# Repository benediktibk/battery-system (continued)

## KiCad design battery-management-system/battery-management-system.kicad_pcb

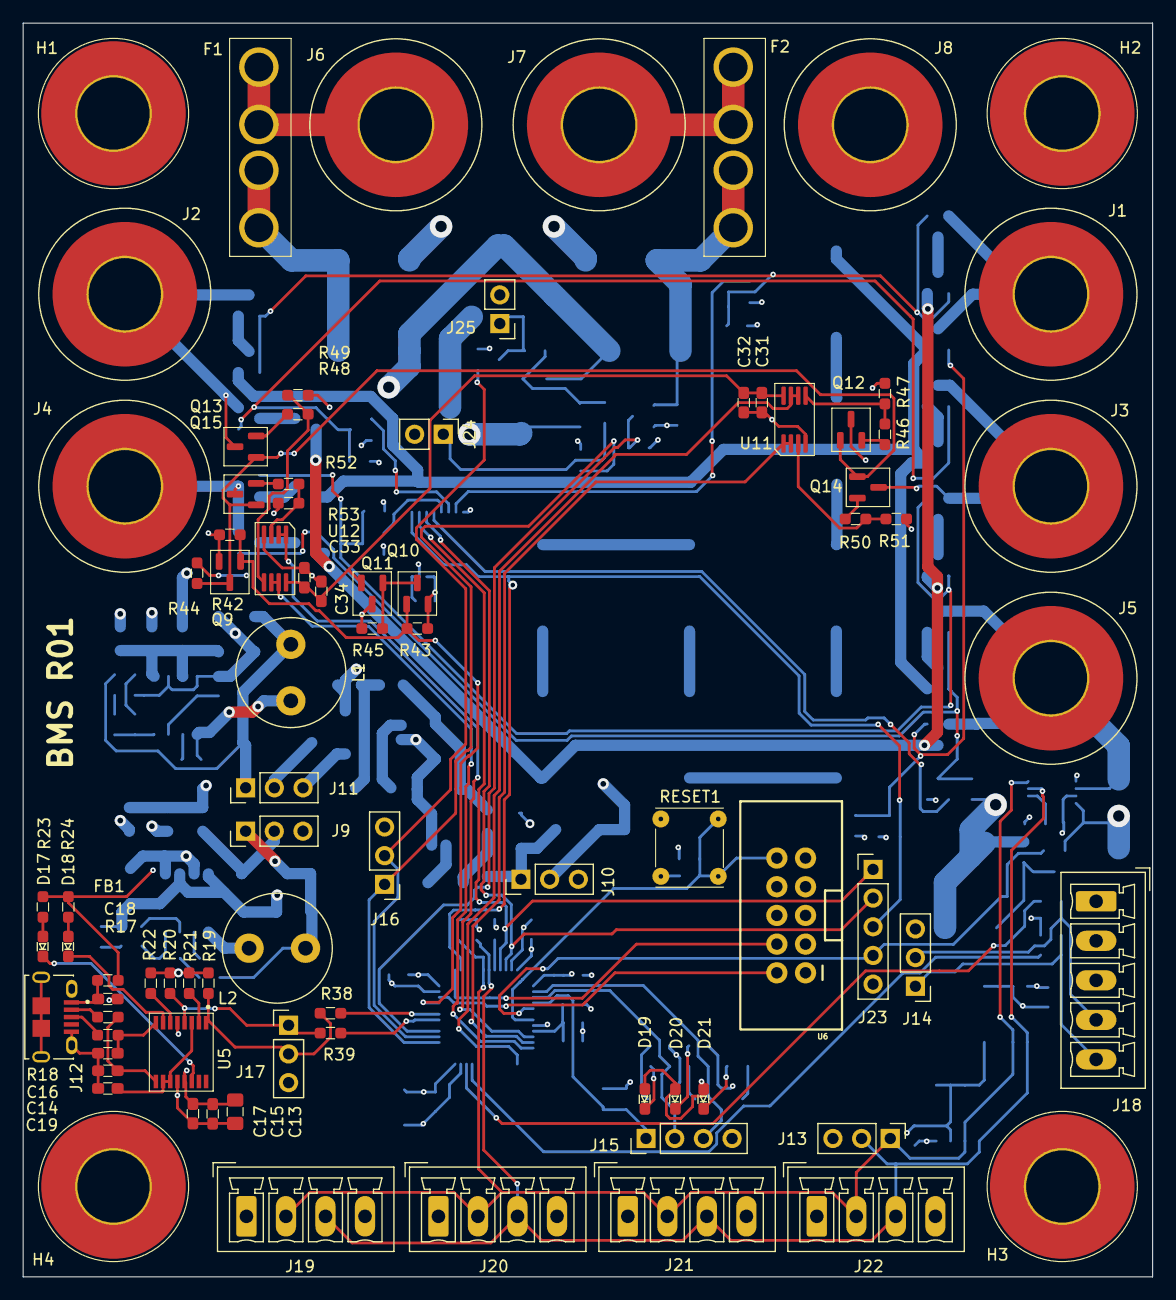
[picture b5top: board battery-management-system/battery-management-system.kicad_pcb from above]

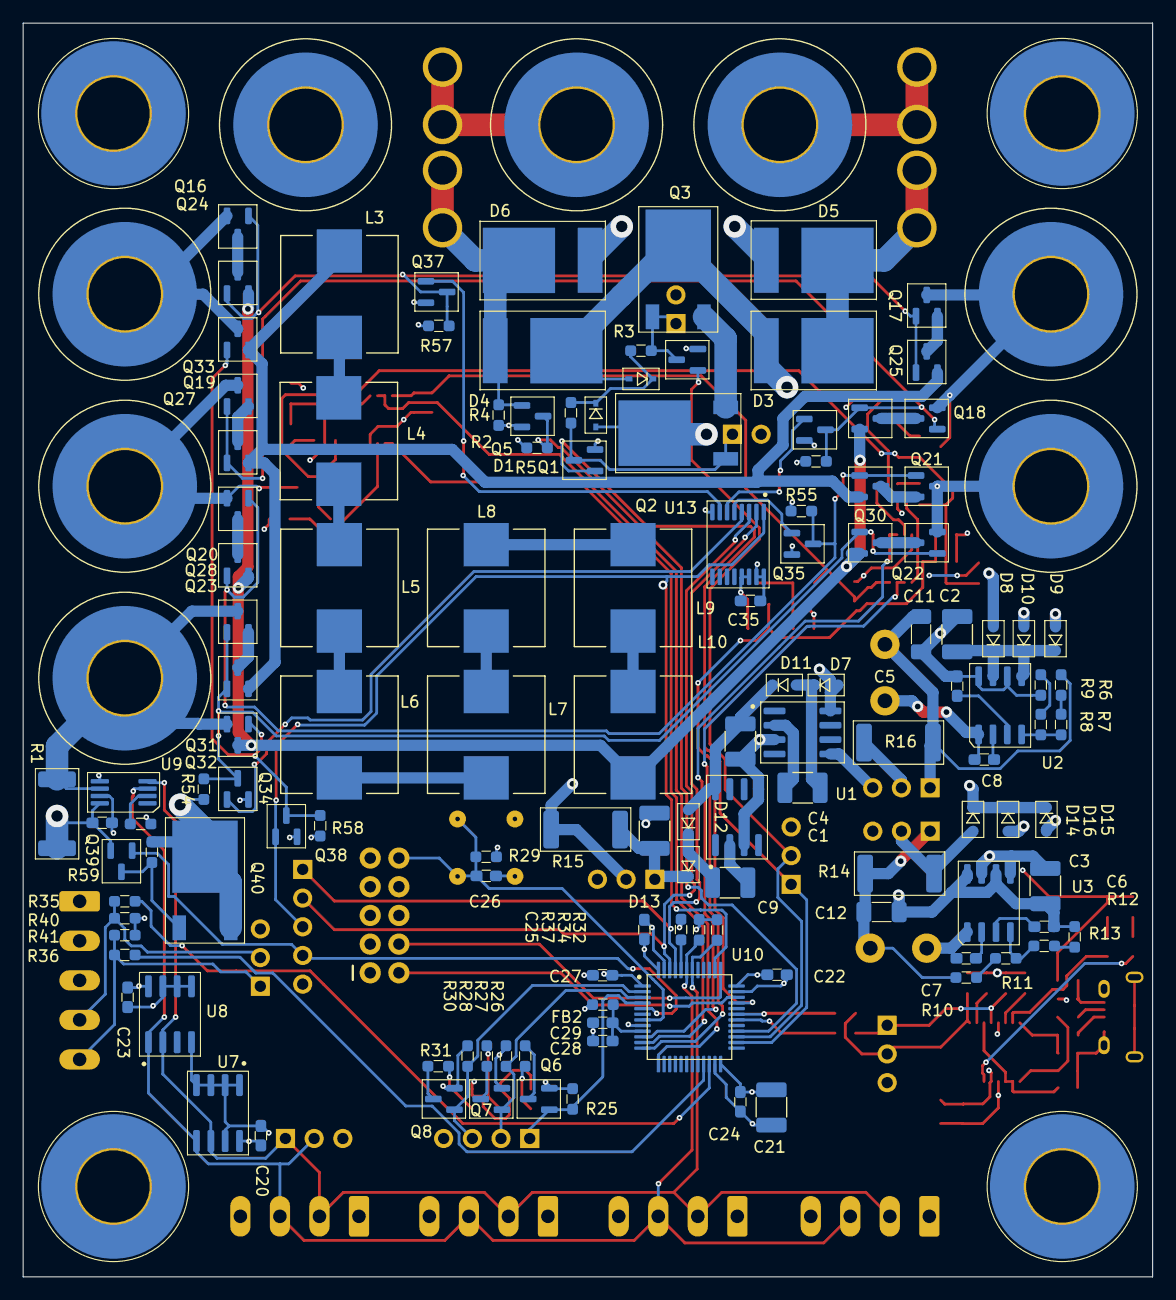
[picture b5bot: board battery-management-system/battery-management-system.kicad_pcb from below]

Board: 4 copper layers, 100.0 x 111.0 mm, 212 parts (128 on the bottom side), 129 nets.

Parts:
C1, C2, C3, C4, C9, C10, C21: 10uF; C_1210_3225Metric_Pad1.33x2.70mm_HandSolder
C5, C6, C29, C30, C32, C34: 1uF; C_0603_1608Metric_Pad1.08x0.95mm_HandSolder
C7, C8, C15, C17, C19, C20, C22, C23, C24, C25, C26, C27, C28, C31, C33, C35: 100nF; C_0603_1608Metric_Pad1.08x0.95mm_HandSolder
C11, C12: 47uF; C_1206_3216Metric_Pad1.33x1.80mm_HandSolder
C13: 4.7uF; C_0805_2012Metric_Pad1.18x1.45mm_HandSolder
C14, C16: 47pF; C_0603_1608Metric_Pad1.08x0.95mm_HandSolder
C18: 10nF; C_0603_1608Metric_Pad1.08x0.95mm_HandSolder
D1, D2, D7, D8, D9, D10, D11, D12, D13, D14, D15, D16: BAT54WS; D_SOD-323
D3, D4, D5, D6: SBR2065D1
D17: UART_TX; D_0603_1608Metric_Pad1.05x0.95mm_HandSolder
D18: UART_RX; D_0603_1608Metric_Pad1.05x0.95mm_HandSolder
D19: green; D_0603_1608Metric_Pad1.05x0.95mm_HandSolder
D20: red; D_0603_1608Metric_Pad1.05x0.95mm_HandSolder
D21: yellow; D_0603_1608Metric_Pad1.05x0.95mm_HandSolder
F1, F2: 20A; KEYSTONE_blade_fus_holder
FB1, FB2: BLM18P; R_0603_1608Metric_Pad0.98x0.95mm_HandSolder
H1, H2, H3, H4: MountingHole_Pad; MountingHole_6.4mm_M6_Pad_TopBottom
J1: CELL4_PLUS; Connector_M6
J2: CELL4_MINUS; Connector_M6
J3: CELL3_MINUS; Connector_M6
J4: CELL2_MINUS; Connector_M6
J5: CELL1_MINUS; Connector_M6
J6: VBAT+; Connector_M6
J7: VBAT+_CHARGE; Connector_M6
J8: VBAT-; Connector_M6
J9: 5V; PinHeader_1x03_P2.54mm_Vertical
J10: 18V; PinHeader_1x03_P2.54mm_Vertical
J11: 3V3; PinHeader_1x03_P2.54mm_Vertical
J12: AMPHENOL_micro_usb_10118194-0001LF; AMPHENOL_10118194-0001LF
J13: I2C; PinHeader_1x03_P2.54mm_Vertical
J14: UART_INTERCONNECT; PinHeader_1x03_P2.54mm_Vertical
J15: LEDS; PinHeader_1x04_P2.54mm_Vertical
J16: CHARGE/DISCHARGE; PinHeader_1x03_P2.54mm_Vertical
J17: UART_USB; PinHeader_1x03_P2.54mm_Vertical
J18: rspro_header_5pin_3_5mm
J19: TEMP_CELL1; rspro_header_4pin_3_5mm
J20: TEMP_CELL2; rspro_header_4pin_3_5mm
J21: TEMP_CELL3; rspro_header_4pin_3_5mm
J22: TEMP_CELL4; rspro_header_4pin_3_5mm
J23: Conn_01x05; PinHeader_1x05_P2.54mm_Vertical
J24: Charge; PinHeader_1x02_P2.54mm_Vertical
J25: Discharge; PinHeader_1x02_P2.54mm_Vertical
L1, L2: 22uH; L_Radial_D9.5mm_P5.00mm_Fastron_07HVP
L3, L4, L5, L6, L7, L8, L9, L10: L_220µH_1A; L_Wuerth_HCI-1050
Q1, Q4, Q5, Q6, Q7, Q8, Q9, Q10, Q16, Q17, Q18, Q19, Q20, Q21, Q22, Q23, Q24, Q25, Q26, Q27, Q28, Q29, Q30, Q31, Q32, Q33, Q34, Q35, Q36, Q37, Q38, Q39: DMN3404L; SOT-23
Q2, Q3, Q40: TJ40S04M3L; TO-252-2
Q11, Q12, Q13, Q14, Q15: BS250FTA; SOT-23
R1, R14, R15, R16: 2mOhm; R_2512_6332Metric_Pad1.40x3.35mm_HandSolder
R2, R3, R42, R43, R44, R45, R59: 220kOhm; R_0603_1608Metric_Pad0.98x0.95mm_HandSolder
R4, R5, R7, R11, R19, R20, R21, R22, R25, R27, R29, R30, R37, R40, R41, R54, R55, R56, R57, R58: 10kOhm; R_0603_1608Metric_Pad0.98x0.95mm_HandSolder
R6, R10: 390kOhm; R_0603_1608Metric_Pad0.98x0.95mm_HandSolder
R8, R46, R48, R50, R53: 100kOhm; R_0603_1608Metric_Pad0.98x0.95mm_HandSolder
R9, R13: 39kOhm; R_0603_1608Metric_Pad0.98x0.95mm_HandSolder
R12: 43kOhm; R_0603_1608Metric_Pad0.98x0.95mm_HandSolder
R17, R18: 27Ohm; R_0603_1608Metric_Pad0.98x0.95mm_HandSolder
R23, R24: 120Ohm; R_0603_1608Metric_Pad0.98x0.95mm_HandSolder
R26, R28, R31: 100Ohm; R_0603_1608Metric_Pad0.98x0.95mm_HandSolder
R32, R34: 4.7kOhm; R_0603_1608Metric_Pad0.98x0.95mm_HandSolder
R33: 200kOhm; R_0603_1608Metric_Pad0.98x0.95mm_HandSolder
R35, R36, R38, R39: 0Ohm; R_0603_1608Metric_Pad0.98x0.95mm_HandSolder
R47, R52: 24kOhm; R_0603_1608Metric_Pad0.98x0.95mm_HandSolder
R49: 36kOhm; R_0603_1608Metric_Pad0.98x0.95mm_HandSolder
R51: 68kOhm; R_0603_1608Metric_Pad0.98x0.95mm_HandSolder
RESET1: TMG1-01
U1, U4: ICL7660; SOIC-8_3.9x4.9mm_P1.27mm
U2, U3: L6982C33DR; SO-8_3.9x4.9mm_P1.27mm
U5: FT230XS; SSOP-16_3.9x4.9mm_P0.635mm
U6: ARM-JTAG-SWD; ARM-JTAG-10-SWD-IDC
U7: AT24C512C; SOIC-8_3.9x4.9mm_P1.27mm
U8: NCT75DR2G; SOIC-8_3.9x4.9mm_P1.27mm
U9: STC3100; MSOP-8_3x3mm_P0.65mm
U10: STM32L071CZTx; LQFP-48_7x7mm_P0.5mm
U11, U12: LM2904M8-13; MSOP-8_3x3mm_P0.65mm
U13: MC74VHC139; TSSOP-16_4.4x5mm_P0.65mm

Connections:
/3V3: C20.1, C21.1, C22.1, C23.1, C24.1, C25.1, C27.1, C30.1, C35.1, D19.2 (A), D20.2 (A), D21.2 (A), FB2.2, J11.2, J19.1, J20.1, J21.1, J22.1, R5.1, R16.1, R19.1, R20.1, R21.1, R22.1, R29.1, R32.1, R34.1, R40.1, R41.1, U6.VREF, U7.8 (V_{CC}), U8.8 (V_{CC}), U9.7 (VCC), U10.1 (VDD), U10.24 (VDD), U10.36 (VDDIO2), U10.48 (VDD), U13.15 (Eb), U13.16 (V_{CC})
/5V: D7.2 (A), D14.1 (K), D15.1 (K), D16.1 (K), J18.2, Q11.3 (S), R45.1, U1.8 (V+)
/5V_EXT: D9.2 (A), D15.2 (A), J18.3
/5V_USB: C13.1, C15.1, C17.1, D10.2 (A), D16.2 (A), FB1.2, R23.1, R24.1, U5.12 (VCC)
/18V: J10.2, Q40.2 (D), Q40.3 (S), R15.1, R44.1, R54.1, R55.1, R56.1, R57.1, R58.1, R59.1
/Battery Pack/CELL1_MINUS: J5.1, Q23.3 (D), Q32.2 (S), R1.1, U9.6 (CG)
/Battery Pack/CELL2_MINUS: J4.1, Q15.3 (S), Q21.3 (D), Q22.2 (S)
/Battery Pack/CELL3_MINUS: J3.1, Q14.3 (S), Q19.3 (D), Q20.2 (S)
/Battery Pack/CELL4_MINUS: J2.1, Q13.3 (S), Q17.3 (D), Q18.2 (S)
/Battery Pack/CHARGE_AVAILABLE: Q5.3 (D), R5.2, U10.28 (PB15)
/Battery Pack/PACK: D1.2 (A), J1.1, Q2.2 (D), Q12.3 (S), Q16.2 (S), Q33.3 (D)
/CELL_BALANCING_A0: J23.1, U10.45 (PB8), U13.2 (A0a)
/CELL_BALANCING_A1: J23.2, U10.46 (PB9), U13.3 (A1a)
/CELL_BALANCING_STROBE: J23.3, Q38.1 (G), U10.38 (PA15), U13.1 (Ea)
/CHARGE: J16.1, Q1.1 (G), U10.26 (PB13)
/Cell Balancing/CHARGE_CELL1: Q22.1 (G), Q23.1 (G), Q30.1 (G), Q31.1 (G), Q34.3 (D), R54.2
/Cell Balancing/CHARGE_CELL2: Q20.1 (G), Q21.1 (G), Q28.1 (G), Q29.1 (G), Q35.3 (D), R55.2
/Cell Balancing/CHARGE_CELL3: Q18.1 (G), Q19.1 (G), Q26.1 (G), Q27.1 (G), Q36.3 (D), R56.2
/Cell Balancing/CHARGE_CELL4: Q16.1 (G), Q17.1 (G), Q24.1 (G), Q25.1 (G), Q37.3 (D), R57.2
/Cell Balancing/DISCHARGE: Q32.1 (G), Q33.1 (G), Q38.3 (D), R58.2
/Cell Measurement/CELL1: U10.10 (PA0), U12.1, U12.2 (-)
/Cell Measurement/CELL2: U10.11 (PA1), U11.1, U11.2 (-)
/Cell Measurement/CELL3: U10.12 (PA2), U12.6 (-), U12.7
/Cell Measurement/CELL4: U10.13 (PA3), U11.6 (-), U11.7
/DISCHARGE: J16.2, Q4.1 (G), U10.27 (PB14)
/EN_CELL_BALANCING: J23.4, Q39.1 (G), U10.5 (PH0)
/EN_CELL_MEASUREMENT: Q9.1 (G), Q10.1 (G), R42.1, R43.1, U10.33 (PA12)
/Interconnect/UART_RX: J14.2, J18.4, R35.1, R40.2
/Interconnect/UART_TX: J14.1, J18.5, R36.1, R41.2
/MCU/LED1: J15.1, Q6.1 (G), R25.2, U10.4 (PC15)
/MCU/LED2: J15.2, Q7.1 (G), R27.2, U10.3 (PC14)
/MCU/LED3: J15.3, Q8.1 (G), R30.2, U10.2 (PC13)
/MCU/NRST: C26.1, R29.2, RESET1.3 (B), RESET1.4 (B), U6.RESET, U10.7 (NRST)
/MCU/SCL: J13.1, J19.2, J20.2, J21.2, J22.2, R32.2, U7.6 (SCL), U8.2 (SCL), U9.4 (SCL), U10.42 (PB6)
/MCU/SDA: J13.2, J19.3, J20.3, J21.3, J22.3, R34.2, U7.5 (SDA), U8.1 (SDA), U9.3 (SDA), U10.43 (PB7)
/MCU/SWCLK: U6.SWCLK, U10.37 (PA14)
/MCU/SWDIO: U6.SWDIO, U10.34 (PA13)
/MCU/UART_USB_RX: J17.2, R19.2, R38.2, U5.1 (TXD)
/MCU/UART_USB_TX: J17.1, R20.2, R39.2, U5.4 (RXD)
/MCU/VDDA: C28.1, C29.1, FB2.1, U10.9 (VDDA)
/PACK_EXT: C3.1, D2.2 (A), D3.1 (A), D4.2 (K), D8.2 (A), Q3.2 (D), U3.5 (EN/CLKN), U3.7 (VIN)
/Power Supply/9V4: C4.1, D11.1 (K), D12.2 (A), U4.8 (V+)
GND: C2.2, C3.2, C4.2, C5.2, C6.2, C10.2, C11.2, C12.2, C13.2, C14.2, C15.2, C16.2, C17.2, C18.2, C19.2, C20.2, C21.2, C22.2, C23.2, C24.2, C25.2, C26.2, C27.2, C28.2, C29.2, C30.2, C31.2, C32.2, C33.2, C34.2, C35.2, D5.1 (A), D6.1 (A), H1.1, H2.1, H3.1, H4.1, J8.1, J9.3, J10.3, J11.3, J12.5 (GND), J12.S1 (SHIELD), J12.S2 (SHIELD), J12.S3 (SHIELD), J12.S4 (SHIELD), J12.S5 (SHIELD), J12.S6 (SHIELD), J13.3, J14.3, J15.4, J16.3, J17.3, J18.1, J19.4, J20.4, J21.4, J22.4, J23.5, J24.2, J25.2, Q1.2 (S), Q4.2 (S), Q5.2 (S), Q6.2 (S), Q7.2 (S), Q8.2 (S), Q9.2 (S), Q10.2 (S), Q34.2 (S), Q35.2 (S), Q36.2 (S), Q37.2 (S), Q38.2 (S), Q39.2 (S), R1.2, R4.2, R9.2, R13.2, R25.1, R27.1, R30.1, R33.2, R37.1, R42.2, R43.2, R47.2, R49.2, R51.2, R53.2, RESET1.1 (A), RESET1.2 (A), U1.3 (GND), U1.5 (V_{OUT}), U2.6 (AGND), U2.8 (PGND), U3.6 (AGND), U3.8 (PGND), U4.3 (GND), U4.5 (V_{OUT}), U5.5 (GND), U5.13 (GND), U6.GND@1 (GND), U6.GND@2 (GND), U6.GND@3 (GND), U7.1 (A0), U7.2 (A1), U7.3 (A2), U7.4 (GND), U7.7 (WP), U8.4 (GND), U8.5 (A2), U8.6 (A1), U8.7 (A0), U9.5 (GND), U9.8 (VIN), U10.8 (VSSA), U10.23 (VSS), U10.35 (VSS), U10.47 (VSS), U11.4 (V-), U12.4 (V-), U13.8 (GND), U13.13 (A1b), U13.14 (A0b)
unnamed: D1.1 (K), D2.1 (K), R2.1, R3.1
unnamed: D3.2 (K), D5.2 (K), F1.2
unnamed: D4.1 (A), D6.2 (K), F2.2, Q5.1 (G), R4.1
unnamed: C2.1, D8.1 (K), D9.1 (K), D10.1 (K), U2.5 (EN/CLKN), U2.7 (VIN)
unnamed: C1.1, D7.1 (K), D11.2 (A)
unnamed: C9.1, D12.1 (K), D13.2 (A)
unnamed: C10.1, D13.1 (K), J10.1, R15.2
unnamed: D14.2 (A), J9.2, R14.1
unnamed: D17.2 (A), R23.2
unnamed: D17.1 (K), U5.14 (CBUS1)
unnamed: D18.2 (A), R24.2
unnamed: D18.1 (K), U5.7 (CBUS2)
unnamed: D19.1 (K), R26.1
unnamed: D20.1 (K), R28.1
unnamed: D21.1 (K), R31.1
unnamed: F1.1, J6.1
unnamed: F2.1, J7.1
unnamed: C12.1, J9.1, L2.1, R10.1, R14.2
unnamed: C11.1, J11.1, L1.1, R6.1, R16.2
unnamed: J12.3 (D+), R18.2
unnamed: J12.2 (D-), R17.2
unnamed: C18.1, FB1.1, J12.1 (VCC)
unnamed: J24.1, Q1.3 (D), Q2.1 (G), R2.2
unnamed: J25.1, Q3.1 (G), Q4.3 (D), R3.2
unnamed: L3.2, L4.1
unnamed: L4.2, L5.1
unnamed: L5.2, L6.1
unnamed: L6.2, L7.1
unnamed: L7.2, L8.1
unnamed: L8.2, L9.1
unnamed: L9.2, L10.1
unnamed: Q2.3 (S), Q3.3 (S)
unnamed: Q6.3 (D), R26.2
unnamed: Q7.3 (D), R28.2
unnamed: Q8.3 (D), R31.2
unnamed: Q10.3 (D), Q11.1 (G), R45.2
unnamed: C31.1, C32.1, C33.1, C34.1, Q11.2 (D), U11.8 (V+), U12.8 (V+)
unnamed: Q12.2 (D), R46.1
unnamed: Q9.3 (D), Q12.1 (G), Q13.1 (G), Q14.1 (G), Q15.1 (G), R44.2
unnamed: Q13.2 (D), R48.1
unnamed: Q14.2 (D), R50.1
unnamed: Q15.2 (D), R52.1
unnamed: Q16.3 (D), Q24.3 (D)
unnamed: Q17.2 (S), Q25.3 (D)
unnamed: Q18.3 (D), Q26.3 (D)
unnamed: Q19.2 (S), Q27.3 (D)
unnamed: Q20.3 (D), Q28.3 (D)
unnamed: Q21.2 (S), Q29.3 (D)
unnamed: Q22.3 (D), Q30.3 (D)
unnamed: Q23.2 (S), Q31.3 (D)
unnamed: L10.2, Q24.2 (S), Q26.2 (S), Q28.2 (S), Q30.2 (S), Q32.3 (D)
unnamed: L3.1, Q25.2 (S), Q27.2 (S), Q29.2 (S), Q31.2 (S), Q33.2 (S)
unnamed: Q34.1 (G), U13.4 (Y0a)
unnamed: Q35.1 (G), U13.5 (Y1a)
unnamed: Q36.1 (G), U13.6 (Y2a)
unnamed: Q37.1 (G), U13.7 (Y3a)
unnamed: Q39.3 (D), Q40.1 (G), R59.2
unnamed: R6.2, R7.1
unnamed: R8.2, R9.1
unnamed: R10.2, R11.1
unnamed: R12.2, R13.1
unnamed: C1.2, U1.2 (CAP+)
unnamed: C8.2, U2.2 (BOOT)
unnamed: R7.2, R8.1, U2.4 (FB/VOUT)
unnamed: C8.1, L1.2, U2.1 (SW)
unnamed: C5.1, U2.3 (VCC)
unnamed: C7.2, U3.2 (BOOT)
unnamed: R11.2, R12.1, U3.4 (FB/VOUT)
unnamed: C7.1, L2.2, U3.1 (SW)
unnamed: C6.1, U3.3 (VCC)
unnamed: C9.2, U4.2 (CAP+)
unnamed: C19.1, U5.3 (VCCIO), U5.10 (3V3OUT), U5.11 (~RESET)
unnamed: C14.1, R17.1, U5.9 (USBDM)
unnamed: C16.1, R18.1, U5.8 (USBDP)
unnamed: R22.2, U5.6 (~CTS)
unnamed: R21.2, U5.2 (~RTS)
unnamed: R33.1, U9.2 (ROSC)
unnamed: R37.2, U10.44 (BOOT0)
unnamed: R39.1, U10.30 (PA9)
unnamed: R38.1, U10.31 (PA10)
unnamed: R36.2, U10.21 (PB10)
unnamed: R35.2, U10.22 (PB11)
unnamed: R50.2, R51.1, U11.3 (+)
unnamed: R46.2, R47.1, U11.5 (+)
unnamed: R52.2, R53.1, U12.3 (+)
unnamed: R48.2, R49.1, U12.5 (+)

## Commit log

2023-08-13 add initial battery management system
2023-08-13 add gitignore
2023-08-13 add USB and debug connectors
2023-10-15 add simulation for charge and discharge FETs
2023-10-15 add charge and discharge FETs
2023-10-15 add calculation spread sheet
2023-10-15 remove temporary net
2023-10-15 specify forward voltage of diode
2023-10-18 select diode for charge and discharge FETs
2023-10-18 introduce hierarchical sheets
2023-10-19 define basic hierarchy and power supplies
2023-10-20 enable 5V with VIN
2023-10-20 add RS order numbers
2023-10-20 add missing order numbers
2023-10-21 define current sense resistance value
2023-10-21 use own symbols and footprints
2023-10-21 use correct symbol for current sense resistor
2023-10-21 specify footprints for resistors, capacitors and inductances
2023-10-21 specify footprint for 47uF capacitor
2023-10-21 use M6 connectors, update symbols
2023-10-21 automatically import schematic into PCB
2023-10-21 add first attempt for balance FET circuit
2023-10-22 add second version of active balancing circuit
2023-10-22 update PCB
2023-10-22 simulate balance circuit with inductor
2023-10-22 control balance fets with smaller control voltage
2023-10-22 dimension balance circuit approach with inductance
2023-10-22 simulate balancing circuit with capacitor bank
2023-10-22 tune balance circuit simulation
2023-10-22 use only nmos in balance FET simulation
2023-10-22 calculate balancing with FETs
2023-11-12 create schematic for USB
2023-11-13 add resistors, capacitors and LEDs
2023-11-13 implement interconnect
2023-11-14 implement cell measurement
2023-11-14 route UART and ADC channels on MCU
2023-11-19 add power supply for MCU
2023-11-21 add temperature sensor and LEDs
2023-11-22 calculate balancing with reed relais
2023-11-22 improve calculation of balancing
2023-11-23 add components
2023-11-23 improve usage of net labels
2023-11-24 add 20V supply
2023-11-24 add balancing sheet
2023-11-24 implement balancing
2023-11-24 add fuel gauge IC
2023-11-24 fix electrical rule checker errors
2023-11-24 fix current sensing
2023-11-25 add negative power supply for OPAMPs
2023-11-25 implement negative power supply for OPAMPs
2023-11-25 fix ERC issues
2023-11-25 fix PCB errors
2023-11-25 improve placement
2023-11-26 place and route
2023-11-27 retry layout
2023-11-27 start with routing of USB
2023-11-27 route power routes
2023-11-27 route USB
2023-11-27 place balance caps and relais
2023-11-27 work on layout
2023-11-27 finish first draft of layout
2023-11-29 fix design rule errors
2023-11-30 update mounting hole footpring
2023-11-30 update ignore settings
2023-12-01 apply recommendations of Stefan
2023-12-01 remove net classes
2023-12-01 improve silkscreen
2023-12-01 improve layout
2023-12-02 improve fabrication layers
2023-12-02 finish routing
2023-12-02 improve silkscreen and fab
2023-12-02 add label and version to silkscreen
2023-12-02 add cell temperature sensor PCB
2023-12-02 add project for DC DC converter PCB
2023-12-02 add 3D model of supercap
2023-12-03 update footprints and layout
2023-12-04 update BOM
2023-12-13 add option for balancing with an inductor
2023-12-13 add another option for balancing with an inductor
2023-12-26 simplify cell measurement
2023-12-26 develop inductance based balance methods
2023-12-28 switch to inductor based cell balancing
2023-12-29 finish cell balancing changes
2023-12-29 fix electrical rule check errors
2023-12-29 add enable input for cell measurement
2023-12-29 make layout easier for cell measurement
2023-12-29 finish layout of cell measurement
2023-12-29 finish placement and layout of supplies
2023-12-29 place and partial route USB
2023-12-29 add overrides for charge and discharge
2023-12-29 place USB again
2023-12-29 continue with layout
2023-12-30 improve routing of power supply
2023-12-30 generate fabrication outputs
2023-12-30 fix silkscreen
2023-12-30 improve fab layers
2023-12-30 create fabrication outputs for R01
2023-12-30 update R01 fabrication outputs of celltemperature sensor and battery-management-system
2024-01-02 start with DC-DC converter
2024-01-02 add fabrication outputs to version control
2024-01-02 update symbol in DC-DC converter
2024-02-16 rename devices in BMS
2024-02-18 add list of design errors for BMS R01
2024-02-18 work on DC DC converter
2024-02-18 continue with design of DC-DC converter
2024-02-21 select MOSFETs for DC-DC converter
2024-02-21 improve output filter of DC-DC converter
2024-02-21 update symbols and footprints
2024-02-24 extend design errors
2024-02-25 extend list of design errors
2024-02-26 add edge cuts
2024-02-27 define missing pull downs in design errors
2024-03-11 extend design errors list
2024-03-11 move hardware into dedicated folder
2024-03-11 initialize west workspace
2024-03-11 update zephyr revision
2024-03-12 add basics for board of battery management system
2024-03-15 fix build of battery management system
2024-03-15 fix use RAM
2024-03-15 add clang format definition
2024-03-26 add script for flashing with black magic probe
2024-03-26 implement status leds
2024-03-26 configure status LEDs during startup in main
2024-03-26 enable shell
2024-03-26 remove dummy loop in main
2024-03-26 activate more shell features
2024-03-26 activate interconnect UART
2024-03-26 activate I2C
2024-03-26 add external EEPROM
2024-03-28 implement cell voltage measurement
2024-03-28 avoid erase during flashing
2024-03-28 implement cells_measurement
2024-03-28 implement power control
2024-03-28 fix logic level definition of charge available
2024-03-29 add temperature sensors
2024-03-29 add battery monitor
2024-03-29 implement basics for cell_balancer
2024-03-29 check cell voltages
2024-03-29 implement shell command for battery state
2024-03-29 measure cell temperatures in main loop
2024-03-29 implement PWM for cell balancer
2024-03-29 fix PWM channel for cell balancer
2024-03-30 update balancing calculation
2024-03-30 reduce stack sizes
2024-03-30 add script for debugging with gdb
2024-03-30 add makefile targets for debugging
2024-03-31 enable cell temperature measurements
2024-03-31 add design error to list
2024-04-01 enable power control during startup
2024-04-05 relax temperature limits for testing
2024-04-05 start simplifying BMS for R02
2024-04-05 update PCB from schematic
2024-04-05 fix design errors
2024-04-06 add heatsink and fix ERC errors
2024-04-06 layout BMS R02
2024-04-06 route BMS R02
2024-04-06 update footprints
2024-04-06 update design errors list
2024-04-06 fix schematic error in DC-DC converter, add heatsink and mounting holes
2024-04-06 create layout for DC-DC converter
2024-04-06 add version on silkscreen
2024-04-07 update footprint of TMG1-01
2024-04-07 fix RS order number
2024-04-13 add first steps for casing
2024-04-13 create side wall with extrusion
2024-04-13 improve wall
2024-04-13 improve casing walls
2024-04-14 finish sides of casing
2024-04-14 add PCBs to casing
2024-04-16 add PCB mounts
2024-04-16 add PCB mounts and lid
2024-04-16 complete lid
2024-04-16 start with lid mount
2024-04-16 create lid to base mounts
2024-04-16 finalize lid
2024-04-18 add some margin to cells and PCBs
2024-04-21 improve lid mounts
2024-04-21 reduce overall casing size
2024-04-21 add exported meshes for casing
2024-05-19 change default board revision for BMS to R01
2024-05-19 add BMS R02 device tree
2024-05-20 activate cell temperature measurements
2024-05-20 add list of design errors for BMS R02
2024-05-20 document design error
2024-05-20 add workaround for incorrect cell voltages
2024-05-20 set a reasonable maximum temperature for the cells and the PCB
2024-05-30 add simulation for DC DC converter
2024-05-30 fix design errors in DC DC converter
2024-05-30 start with redesign of DC DC converter
2024-05-31 layout DC DC converter
2024-05-31 add 3D models
2024-06-01 replace tracks in power path with zones
2024-06-01 improve layout of DC DC converter
2024-06-01 add fabrication outputs of DC DC converter R02
2024-06-01 add simulation of cell configuration change
2024-06-01 fix cell voltage measurements
2024-06-02 add fuel gauge to BMS
2024-06-02 start with cell balancing in BMS
2025-01-01 start with redesign of DC-DC converter
2025-01-06 finish redesign of schematic of DC-DC converter
2025-01-06 improve cooling for DC-DC converter
2025-01-06 used improved footprints
2025-01-06 flip connectors to bottom
2025-01-08 change type of heatsinks
2025-01-19 finish layout for dc-dc converter
2025-01-19 fix design errors of battery management system R02
2025-01-19 add heatsink to sense resistor
2025-01-25 finish cell balancing schematic
2025-01-25 add snubber circuit
2025-01-26 finish placement of BMS R03
2025-01-26 improve layout of BMS
2025-02-06 continue work on layout of BMS
2025-03-04 finish layout of BMS
2025-03-04 fix silkscreen in BMS layout
2025-03-04 improve silkscreen of BMS
2025-03-04 define BOM attributes
2025-03-04 update symbols from library
2025-03-10 replace reset button, update symbols
2025-03-10 update symbols
2025-03-10 add BOM
2025-03-11 replace inductance of power supplies
2025-03-11 generate BOMs
2025-03-11 update symbols and BOM
2025-03-11 add fabrication outputs for battery management system
2025-03-11 add fabrication outputs for DC-DC converter
2025-03-11 add BOM for cell temperature sensor
2025-03-11 rename fabrication outputs of DC-DC converter
2025-03-11 improve thermal connection of current sense resistor in BMS
2025-03-11 generate fabrication outputs for BMS
2025-03-17 update BOM export settings
2025-06-04 note wrong footprint for EEPROM in design error list
2025-06-05 define BMS R03 board for software
2025-06-05 remove software workaround for faulty cell voltages
2025-06-05 introduce wait time after for enabling the cell measurement
2025-06-05 document bug with sleep during cell measurements
2025-07-02 document improvement of cell measurement with INAs
